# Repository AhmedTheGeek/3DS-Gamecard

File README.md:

# 3DS-Gamecard
Eagle Board for nintendo 3DS Gamecard Cartridge

# Dimensions
All the measurements on this board are 99% acurate they may differ a bit but it doesn't affect the performance of the cartridge when inserted in the 3DS slot.

The only major difference in this design is the height, as the **official card height is 30.40mm** I extended it a bit to be able to solder some headers and test the signals.

# Preview

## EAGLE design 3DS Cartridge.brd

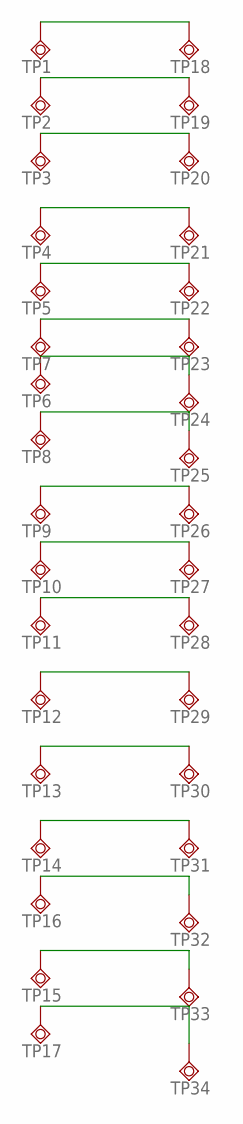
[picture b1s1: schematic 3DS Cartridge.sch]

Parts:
TP1, TP2, TP3, TP4, TP5, TP6, TP7, TP8, TP9, TP10, TP11, TP12, TP13, TP14, TP15, TP16, TP17, TP18, TP19, TP20, TP21, TP22, TP23, TP24, TP25, TP26, TP27, TP28, TP29, TP30, TP31, TP32, TP33, TP34: TPSQTP12SQ; TP12SQ

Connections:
unnamed: TP1.TP, TP18.TP
unnamed: TP2.TP, TP19.TP
unnamed: TP3.TP, TP20.TP
unnamed: TP4.TP, TP21.TP
unnamed: TP5.TP, TP22.TP
unnamed: TP7.TP, TP23.TP
unnamed: TP6.TP, TP24.TP
unnamed: TP8.TP, TP25.TP
unnamed: TP9.TP, TP26.TP
unnamed: TP10.TP, TP27.TP
unnamed: TP11.TP, TP28.TP
unnamed: TP12.TP, TP29.TP
unnamed: TP13.TP, TP30.TP
unnamed: TP14.TP, TP31.TP
unnamed: TP16.TP, TP32.TP
unnamed: TP15.TP, TP33.TP
unnamed: TP17.TP, TP34.TP

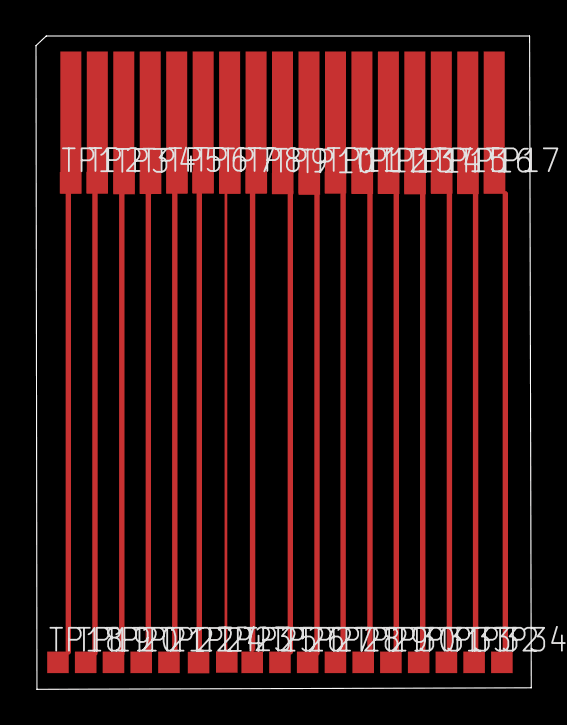
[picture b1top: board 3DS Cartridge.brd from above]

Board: 2 copper layers, 27.5 x 36.3 mm, 34 parts (0 on the bottom side), 17 nets.

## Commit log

2021-05-24 Minor fixes (lines 02, 05)
